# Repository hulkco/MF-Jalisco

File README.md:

# MF-Jalisco
Maker Faire Jalisco 2019

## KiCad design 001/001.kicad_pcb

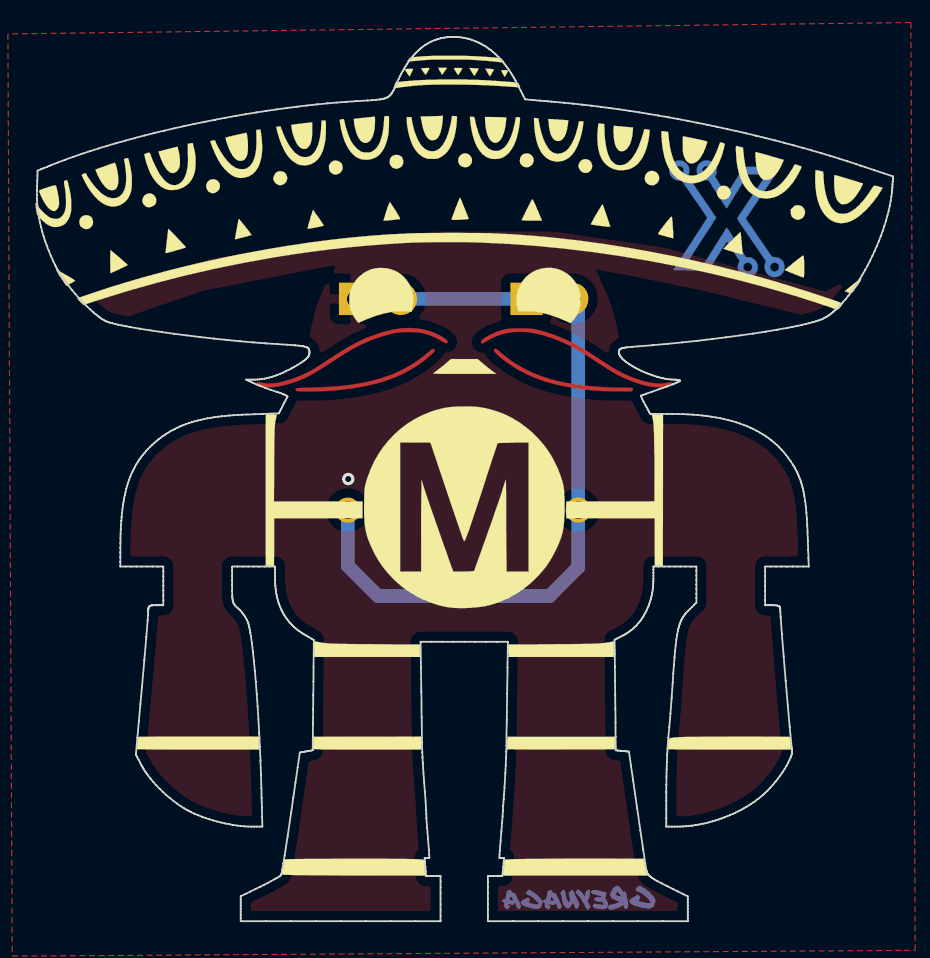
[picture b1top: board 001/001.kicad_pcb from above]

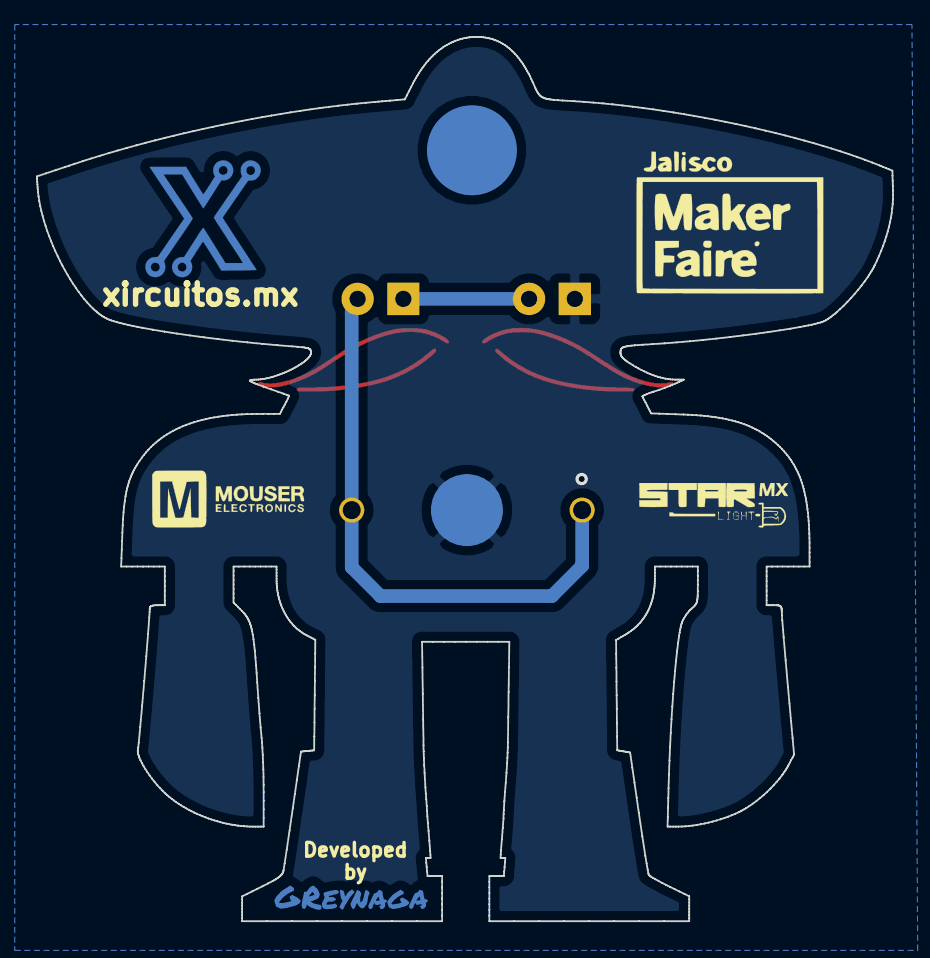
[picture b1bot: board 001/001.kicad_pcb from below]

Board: 2 copper layers, 47.6 x 49.1 mm, 10 parts (3 on the bottom side), 3 nets.

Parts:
BT1: Battery_3V_Coin; CR1220-Jalisco
D1, D2: LED; LED_D5.0mm_FlatTop
Ref**: Val**; MF-Jalisco_Logo_PatrocinioMouser_50mmsvg
Ref**#2: Val**; MF-Jalisco_Logo_50mmsvg
Ref**#3: Val**; MF-Jalisco_Logo_PatrocinioX_50mmsvg
Ref**#4: Val**; MF-Jalisco_Logo_PatrocinioStar_50mmsvg
U1: MF-Jalisco; MF-Jalisco_50mm
U2: Firma; firma_Cu_Mask
U3: PinBase

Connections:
+3V3: BT1.1, D2.2
GND: BT1.2, D1.1
unnamed: D1.2, D2.1

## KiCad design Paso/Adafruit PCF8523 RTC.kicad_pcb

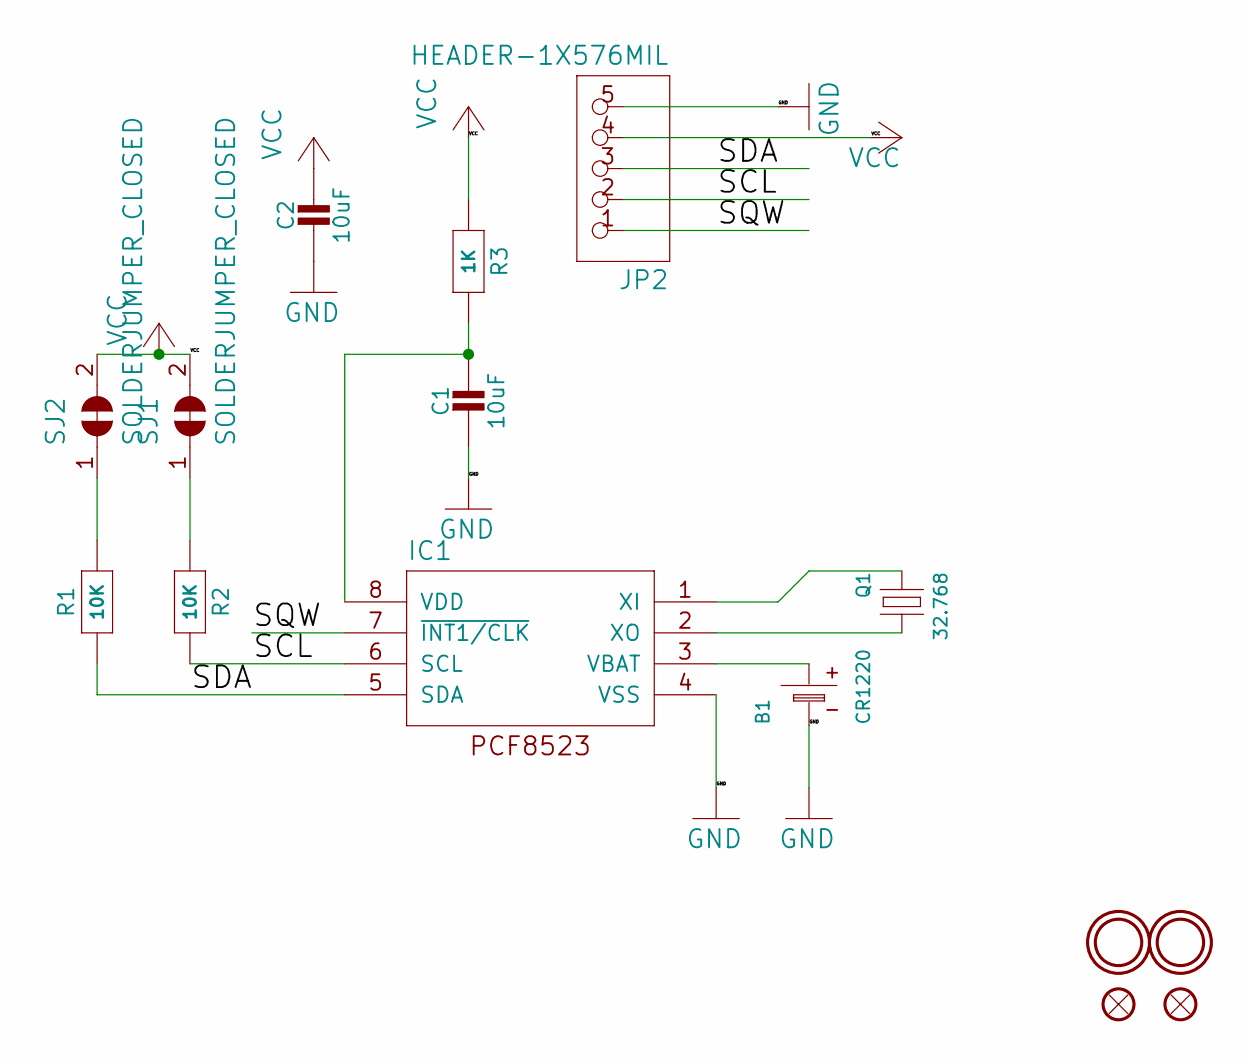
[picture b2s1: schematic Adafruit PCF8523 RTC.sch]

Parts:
B1: CR1220
C1, C2: 10uF; 0805-NO
FID1, FID2: FIDUCIAL\"\"; FIDUCIAL_1MM
IC1: RTC_PCF8523T; SOIC8_150MIL
JP2: HEADER-1X576MIL; 1X05_ROUND_76
Q1: 32.768; CRYSTAL_8X3.8
R1, R2: 10K; 0805-NO
R3: 1K; 0805-NO
SJ1, SJ2: SOLDERJUMPER_CLOSED; SOLDERJUMPER_CLOSEDWIRE
U$1, U$4: MOUNTINGHOLE2.0; MOUNTINGHOLE_2.0_PLATED

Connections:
/SCL: IC1.6 (SCL), JP2.2, R2.2
/SDA: IC1.5 (SDA), JP2.3, R1.1
/SQW: IC1.7 (~INT1/CLK), JP2.1
GND: B1.-, C1.2, C2.2, IC1.4 (VSS), JP2.5
unnamed: B1.+$1 (+), IC1.3 (VBAT)
unnamed: C1.1, IC1.8 (VDD), R3.2
unnamed: IC1.1 (XI), Q1.P$1 (1)
unnamed: IC1.2 (XO), Q1.P$4 (2)
unnamed: R1.2, SJ2.1
unnamed: R2.1, SJ1.1
VCC: C2.1, JP2.4, R3.1, SJ1.2, SJ2.2

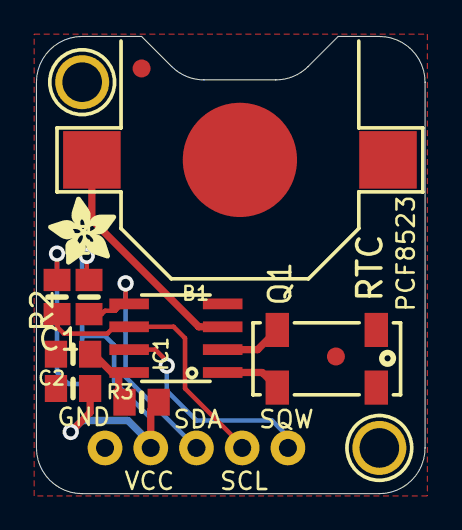
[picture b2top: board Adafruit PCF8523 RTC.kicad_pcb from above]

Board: 16 copper layers, 21.6 x 25.4 mm, 18 parts (0 on the bottom side), 11 nets.

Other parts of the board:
U$2: ADAFRUIT_3.5MM
U$3: PCBFEAT-REV-040
U$5: ADAFRUIT_5MM

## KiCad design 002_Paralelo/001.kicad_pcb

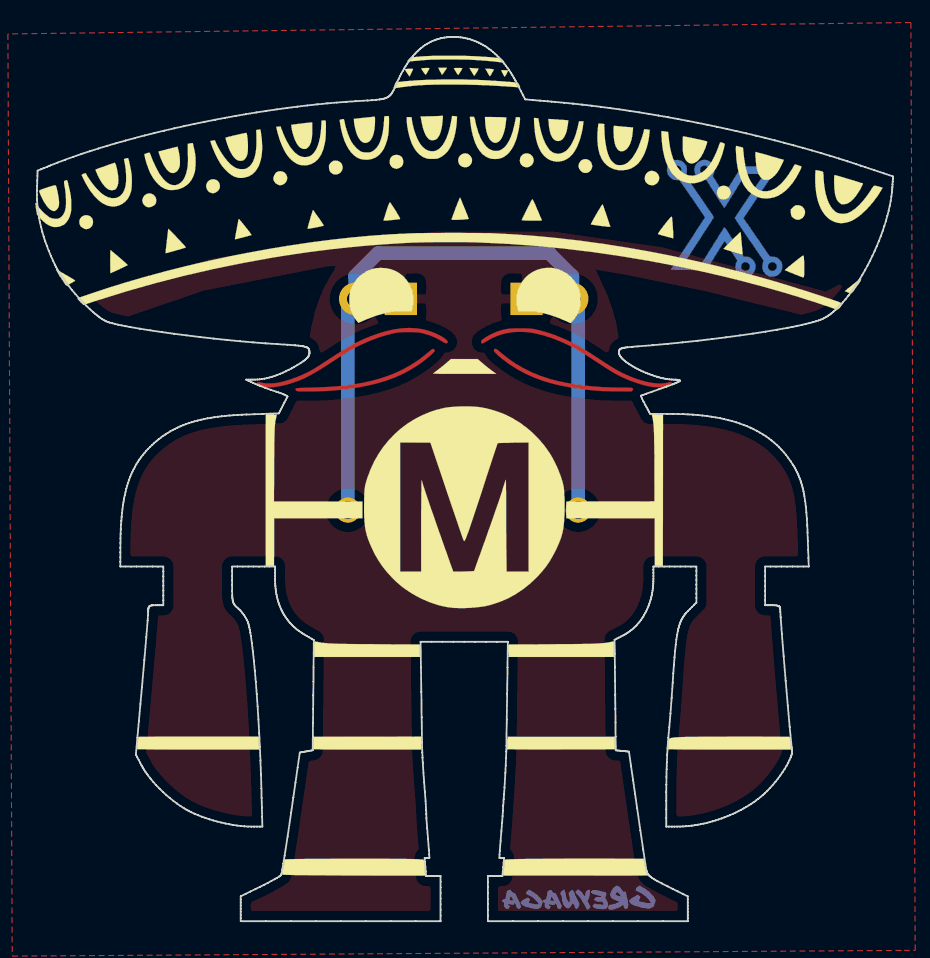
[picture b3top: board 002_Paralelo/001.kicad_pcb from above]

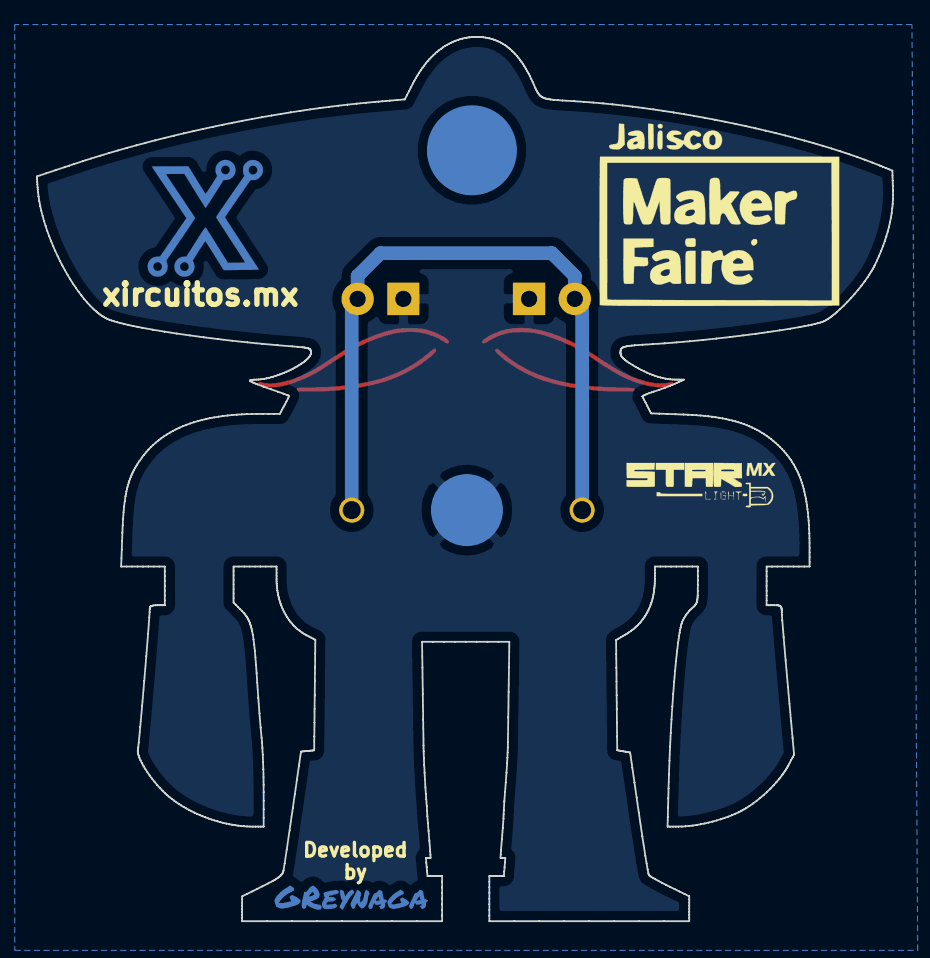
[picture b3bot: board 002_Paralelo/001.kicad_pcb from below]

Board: 2 copper layers, 47.6 x 49.1 mm, 9 parts (3 on the bottom side), 2 nets.

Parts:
BT1: Battery_3V_Coin; CR1220-Jalisco
D1, D2: LED; LED_D5.0mm_FlatTop
U1: MF-Jalisco; MF-Jalisco_50mm
U2: Firma; firma_Cu_Mask
U3: PinBase
U4: Xcircuito; MF-Jalisco_Logo_PatrocinioX_50mmsvg
U5: Start; MF-Jalisco_Logo_PatrocinioStar_50mmsvg
U6: MF-Jalisco; MF-Jalisco_Logo_50mmsvg

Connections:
+3V3: BT1.1, D1.2, D2.2
GND: BT1.2, D1.1, D2.1

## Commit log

2019-08-06 Add Project Files
2019-08-18 Add Battery Holder WA-BCMC and Straw Hat Led
    Add Battery Holder WA-BCMC and Straw Hat Led
2019-08-29 Add Gerbers
2019-09-14 Nuevo porta pila
2019-09-14 Update battery holder
2019-09-25 Add patrocinador X logo
2019-09-27 Minors updates
2019-10-01 Auto stash before merge of "master" and "origin/master"
2019-10-01 Fix Push
2019-10-07 Update MF Logo & add Mouser Logo
2019-10-07 Remove Mouser logo
2019-10-12 Add version en paralelo
2019-11-12 Add France MF
2019-11-12 Add baguette
